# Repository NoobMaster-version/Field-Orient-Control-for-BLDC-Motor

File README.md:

# Field-Orient-Control-for-BLDC-Motor

STM32G431 + DRV8311H BLDC control project using STM32CubeIDE.

## Main components
- `STM32G431CBT6` (MCU)
- `DRV8311H` (3-phase gate driver)
- `AS5600` (magnetic encoder)
- `LDL1117` (voltage regulator)

This repo includes:
- `firmware/3xPWM_FOC` (FOC firmware project)
- `firmware/Open_Loop_Test_DRV8311` (open-loop bring-up test)

## Hardware

### Soldered PCB

### Motor running (open-loop)

## PWM mode (3x PWM)

The firmware uses **3x PWM** with `TIM1` and complementary outputs to drive DRV8311:
- `INHA` from `PA8  (TIM1_CH1)`
- `INHB` from `PA9  (TIM1_CH2)`
- `INHC` from `PA10 (TIM1_CH3)`

- `INLA` from `PB13 (TIM1_CH1N)`
- `INLB` from `PB14 (TIM1_CH2N)`
- `INLC` from `PB15 (TIM1_CH3N)`

## Pin connections (STM32 -> DRV8311 / interface)

### Gate driver control
- `PA8  (TIM1_CH1)`  -> `INHA`
- `PA9  (TIM1_CH2)`  -> `INHB`
- `PA10 (TIM1_CH3)`  -> `INHC`

- `PB13 (TIM1_CH1N)` -> `INLA`
- `PB14 (TIM1_CH2N)` -> `INLB`
- `PB15 (TIM1_CH3N)` -> `INLC`

- `PC13 (GPIO)`      -> `nSLEEP`
- `PC14 (GPIO input)`-> `nFAULT` (pull-up)

### Current sensing
- `PA0 (ADC1_IN1)` -> `SOA`
- `PA1 (ADC2_IN2)` -> `SOB`
- `PA2 (ADC1_IN3)` -> `SOC`

### Encoder and debug
- `PA15 (I2C1_SCL)` -> AS5600 `SCL`
- `PB7  (I2C1_SDA)` -> AS5600 `SDA`
- `PB10 (USART3_TX)` -> UART TX (debug)
- `PB11 (USART3_RX)` -> UART RX (debug)

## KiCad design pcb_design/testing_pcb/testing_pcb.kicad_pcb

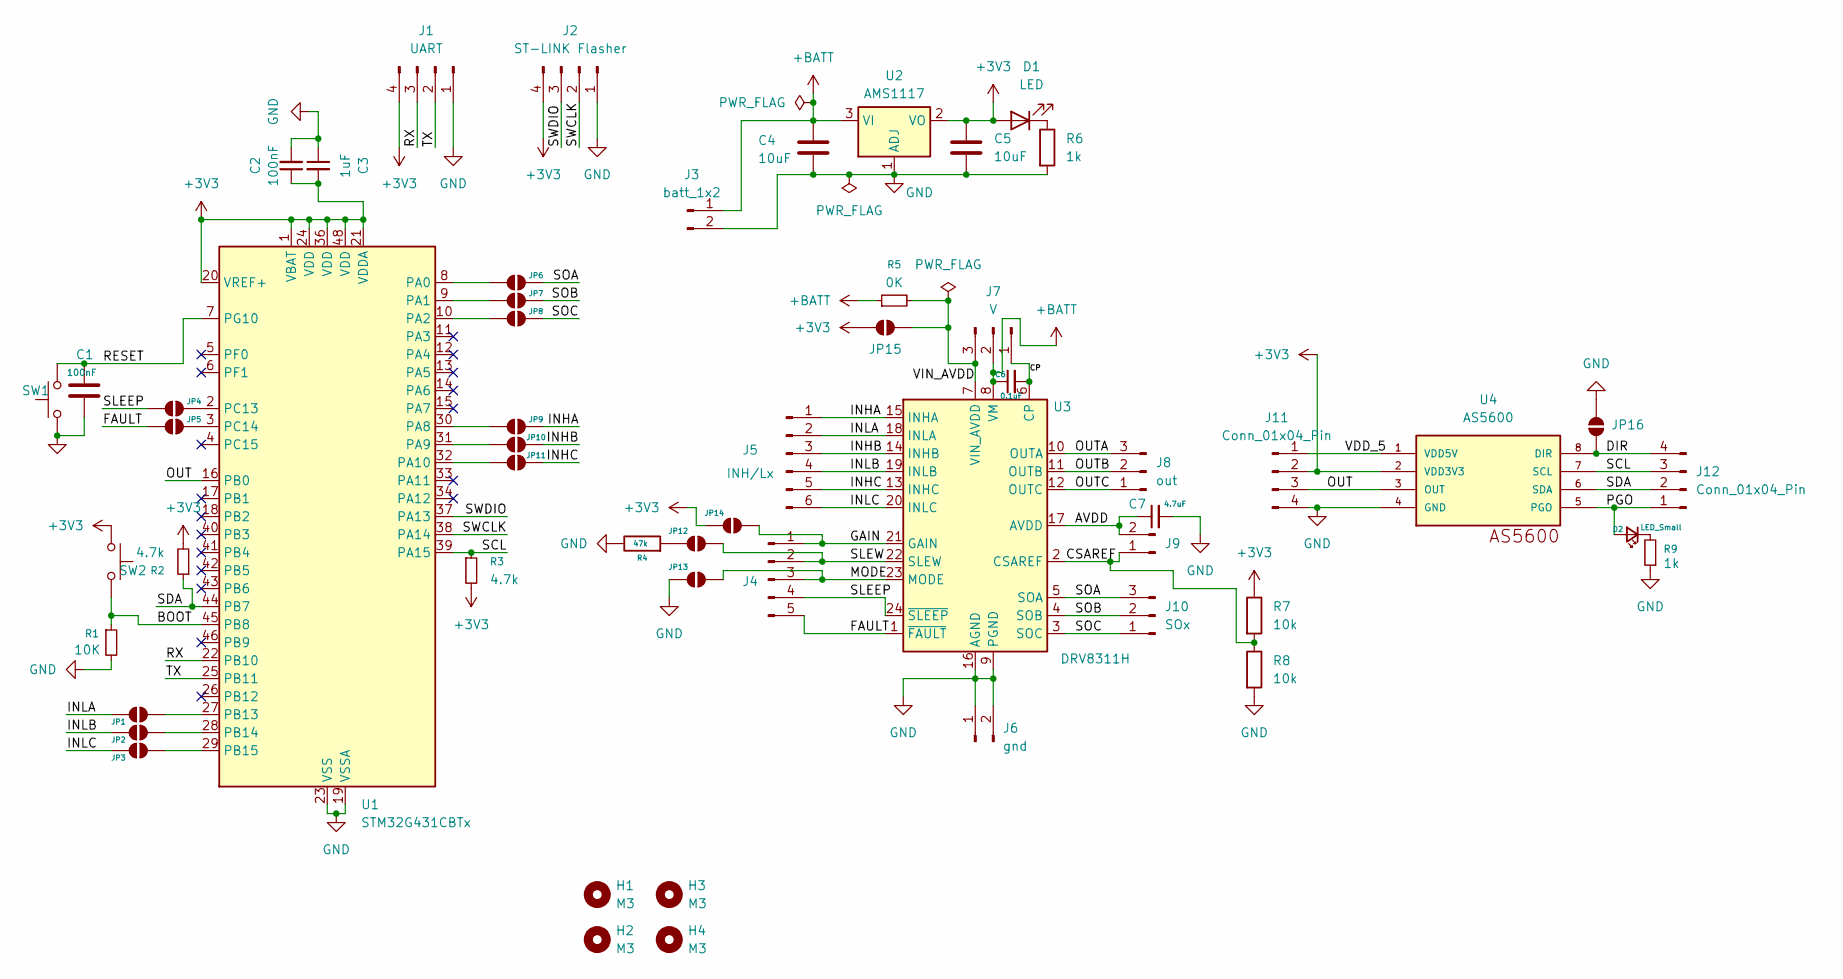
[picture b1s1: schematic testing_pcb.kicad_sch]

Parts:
C1: 100nF; C_0805_2012Metric_Pad1.18x1.45mm_HandSolder
C2: 100nF; C_0805_2012Metric
C3: 1uF; C_0805_2012Metric
C4, C5: 10uF; C_0805_2012Metric
C6: 0.1uF; C_0805_2012Metric
C7: 4.7uF; C_0805_2012Metric
D1: LED; LED_0805_2012Metric
D2: LED_Small; LED_0805_2012Metric
H1, H2, H3, H4: M3; MountingHole_3mm
J1: UART; PinSocket_1x04_P2.54mm_Vertical
J2: ST-LINK Flasher; PinSocket_1x04_P2.54mm_Vertical
J3: batt_1x2; PinSocket_1x02_P2.54mm_Vertical
J4: PinSocket_1x05_P2.54mm_Vertical
J5: INH/Lx; PinSocket_1x06_P2.54mm_Vertical
J6: gnd; PinSocket_1x02_P2.54mm_Vertical
J7: V; PinSocket_1x03_P2.54mm_Vertical
J8: out; PinSocket_1x03_P2.54mm_Vertical
J9: PinSocket_1x02_P2.54mm_Vertical
J10: SOx; PinSocket_1x03_P2.54mm_Vertical
J11, J12: Conn_01x04_Pin; PinSocket_1x04_P2.54mm_Vertical
JP1, JP2, JP3, JP4, JP5, JP6, JP7, JP8, JP9, JP10, JP11, JP12, JP13, JP14, JP15, JP16: SolderJumper_2_Open; SolderJumper-2_P1.3mm_Open_RoundedPad1.0x1.5mm
R1: 10K; R_0805_2012Metric
R2, R3: 4.7k; R_0805_2012Metric
R4: 47k; R_0805_2012Metric
R5: 0K; R_0805_2012Metric
R6: 1k; R_0805_2012Metric
R7, R8: 10k; R_0805_2012Metric
R9: 1k; LED_0805_2012Metric
SW1, SW2: SW_Push; SW_PUSH_6mm_H5mm
U1: STM32G431CBTx; LQFP-48_7x7mm_P0.5mm
U2: AMS1117; SOT-223-3_TabPin2
U3: DRV8311H; Texas_RRW0024A_WQFN-24-1EP_3x3mm_P0.4mm_EP1.9x1.9mm
U4: AS5600; SOIC8

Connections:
+3V3: C2.1, C3.2, C5.1, D1.2 (A), J1.4, J2.4, J11.2, JP14.1 (A), JP15.1 (A), R2.2, R3.2, R7.1, SW2.1, U1.1 (VBAT), U1.20 (VREF+), U1.21 (VDDA), U1.24 (VDD), U1.36 (VDD), U1.48 (VDD), U2.2 (VO), U4.2 (VDD3V3); also elsewhere on the board
+BATT: C4.1, C6.1, J3.1, J7.2, R5.1, U2.3 (VI), U3.8 (VM)
/AVDD: C7.1, J9.2, U3.17 (AVDD)
/BOOT: R1.1, SW2.2, U1.45 (PB8); also elsewhere on the board
/CP: C6.2, J7.1, U3.6 (CP)
/CSAREF: J9.1, R7.2, R8.1, U3.2 (CSAREF)
/DIR: J12.4, JP16.1 (A), U4.8 (DIR)
/FAULT: J4.5, JP5.1 (A), U3.1 (~FAULT)
/GAIN: J4.1, JP14.2 (B), U3.21 (GAIN)
/INHA: J5.1, JP9.2 (B), U3.15 (INHA)
/INHB: J5.3, JP10.2 (B), U3.14 (INHB)
/INHC: J5.5, JP11.2 (B), U3.13 (INHC)
/INLA: J5.2, JP1.2 (B), U3.18 (INLA)
/INLB: J5.4, JP2.2 (B), U3.19 (INLB)
/INLC: J5.6, JP3.2 (B), U3.20 (INLC)
/MODE: J4.3, JP13.2 (B), U3.23 (MODE)
/OUT: J11.3, U1.16 (PB0), U4.3 (OUT)
/OUTA: J8.3, U3.10 (OUTA)
/OUTB: J8.2, U3.11 (OUTB)
/OUTC: J8.1, U3.12 (OUTC)
/PGO: D2.2 (A), J12.1, U4.5 (PGO)
/RESET: C1.1, SW1.2, U1.7 (PG10); also elsewhere on the board
/RX: J1.3, U1.22 (PB10); also elsewhere on the board
/SCL: J12.3, R3.1, U1.39 (PA15), U4.7 (SCL)
/SDA: J12.2, R2.1, U1.44 (PB7), U4.6 (SDA)
/SLEEP: J4.4, JP4.1 (A), U3.24 (~SLEEP)
/SLEW: J4.2, JP12.2 (B), U3.22 (SLEW)
/SOA: J10.3, JP6.2 (B), U3.5 (SOA)
/SOB: J10.2, JP7.2 (B), U3.4 (SOB)
/SOC: J10.1, JP8.2 (B), U3.3 (SOC)
/SWCLK: J2.2, U1.38 (PA14)
/SWDIO: J2.3, U1.37 (PA13)
/TX: J1.2, U1.25 (PB11); also elsewhere on the board
/VDD_5: J11.1, U4.1 (VDD5V)
/VIN_AVDD: J7.3, JP15.2 (B), R5.2, U3.7 (VIN_AVDD)
GND: C1.2, C2.2, C3.1, C4.2, C5.2, C7.2, J1.1, J2.1, J3.2, J6.1, J6.2, J11.4, JP13.1 (A), JP16.2 (B), R1.2, R4.1, R6.2, R8.2, R9.1, SW1.1, U1.19 (VSSA), U1.23 (VSS), U1.35 (VSS), U1.47 (VSS), U2.1 (ADJ), U3.9 (PGND), U3.16 (AGND), U3.25 (PGND), U4.4 (GND); also elsewhere on the board
unnamed: D1.1 (K), R6.1
unnamed: D2.1 (K), R9.2
unnamed: JP1.1 (A), U1.27 (PB13)
unnamed: JP2.1 (A), U1.28 (PB14)
unnamed: JP3.1 (A), U1.29 (PB15)
unnamed: JP4.2 (B), U1.2 (PC13)
unnamed: JP5.2 (B), U1.3 (PC14)
unnamed: JP6.1 (A), U1.8 (PA0)
unnamed: JP7.1 (A), U1.9 (PA1)
unnamed: JP8.1 (A), U1.10 (PA2)
unnamed: JP9.1 (A), U1.30 (PA8)
unnamed: JP10.1 (A), U1.31 (PA9)
unnamed: JP11.1 (A), U1.32 (PA10)
unnamed: JP12.1 (A), R4.2

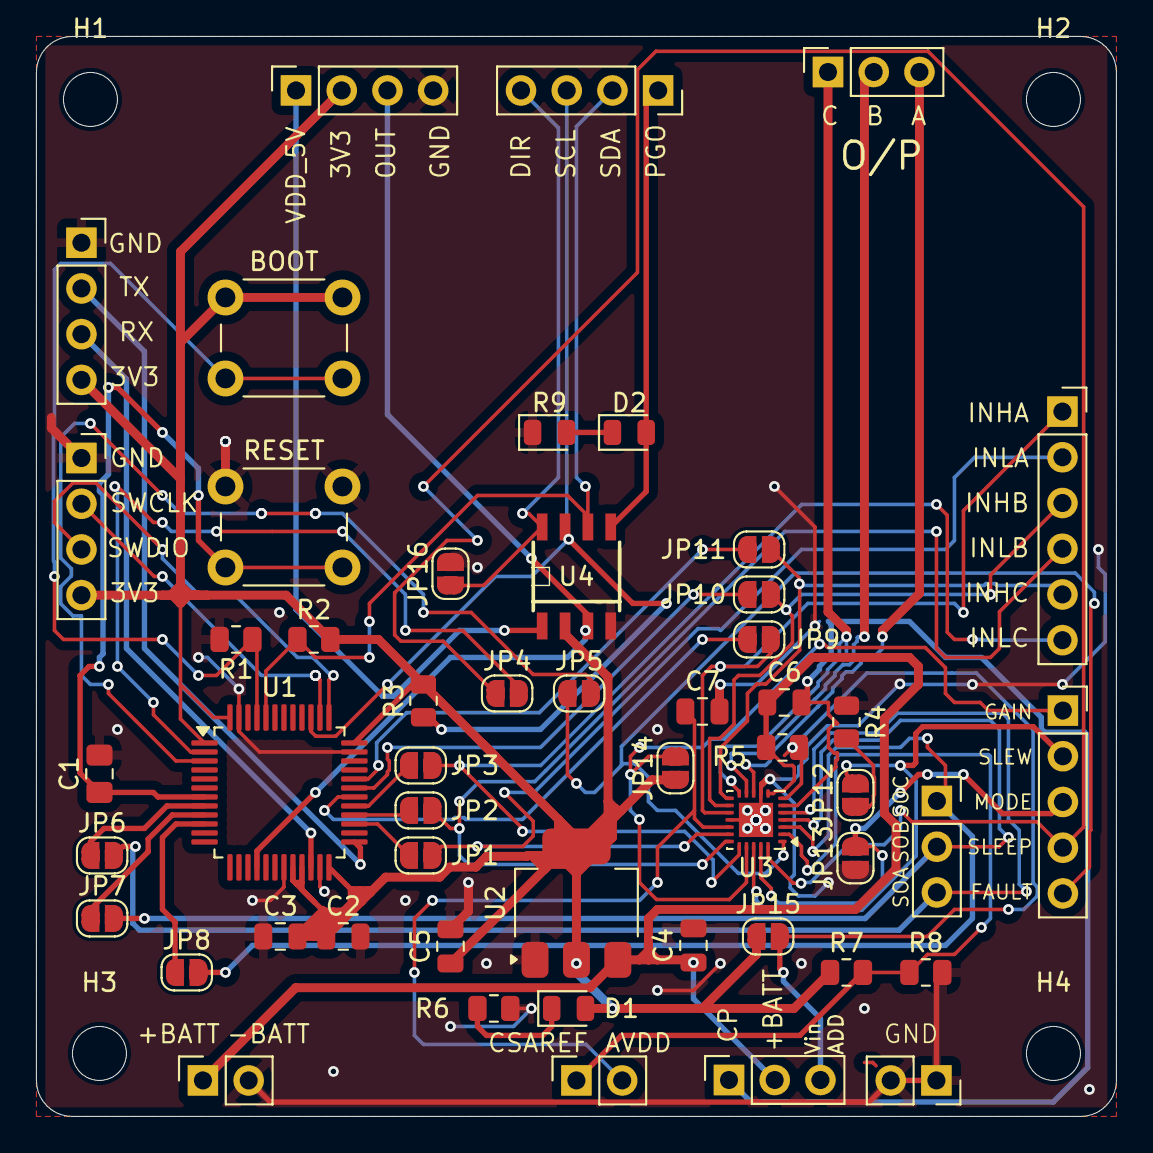
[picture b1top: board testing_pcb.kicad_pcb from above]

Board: 2 copper layers, 60.0 x 60.0 mm, 56 parts (0 on the bottom side), 50 nets.

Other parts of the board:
BOOT: SW_Push; SW_PUSH_6mm_H5mm
GND: UART; PinSocket_1x04_P2.54mm_Vertical
RESET: SW_Push; SW_PUSH_6mm_H5mm

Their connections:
+3V3: BOOT.1, GND.4; also elsewhere on the board
/BOOT: BOOT.2; also elsewhere on the board
/RESET: RESET.2; also elsewhere on the board
/RX: GND.3; also elsewhere on the board
/TX: GND.2; also elsewhere on the board
GND: GND.1, RESET.1; also elsewhere on the board

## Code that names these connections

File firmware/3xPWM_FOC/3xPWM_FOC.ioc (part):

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Mcu.Name=STM32G431C(6-8-B)Tx
Mcu.Package=LQFP48
Mcu.UserName=STM32G431CBTx
PA0.Mode=IN1-Single-Ended
PA0.Signal=ADC1_IN1
PA1.Mode=IN2-Single-Ended
PA1.Signal=ADC2_IN2
PA10.Signal=S_TIM1_CH3
PA15.Mode=I2C
PA15.Signal=I2C1_SCL
PA2.Mode=IN3-Single-Ended
PA2.Signal=ADC1_IN3
PA8.Signal=S_TIM1_CH1
PA9.Signal=S_TIM1_CH2
PB10.Mode=Asynchronous
PB10.Signal=USART3_TX
PB11.Mode=Asynchronous
PB11.Signal=USART3_RX
PB13.GPIOParameters=PinState,GPIO_Speed
PB13.PinState=GPIO_PIN_RESET
PB13.GPIO_Speed=GPIO_SPEED_FREQ_HIGH
PB13.Signal=GPIO_Output
PB14.GPIOParameters=PinState
PB14.PinState=GPIO_PIN_RESET
PB14.Signal=GPIO_Output
PB15.GPIOParameters=PinState
PB15.PinState=GPIO_PIN_RESET
PB15.Signal=GPIO_Output
PB7.Mode=I2C
PB7.Signal=I2C1_SDA
PC13.GPIOParameters=PinState
PC13.PinState=GPIO_PIN_RESET
PC13.Signal=GPIO_Output
PC14-OSC32_IN.GPIOParameters=GPIO_PuPd
PC14-OSC32_IN.GPIO_PuPd=GPIO_PULLUP
PC14-OSC32_IN.Signal=GPIO_Input
RCC.HSE_VALUE=8000000
RCC.SYSCLKFreq_VALUE=170000000
RCC.SYSCLKSource=RCC_SYSCLKSOURCE_PLLCLK
board=custom

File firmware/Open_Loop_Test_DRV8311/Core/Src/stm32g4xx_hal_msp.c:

/* USER CODE BEGIN Header */
/**
  ******************************************************************************
  * @file    stm32g4xx_hal_msp.c
  * @brief   MSP for DRV8311H 3x PWM + AS5600 encoder
  *
  * ============================================================
  *  FIX vs original hal_msp.c
  * ============================================================
  * BUG (original): HAL_TIM_MspPostInit initialised PB13/14/15 LOW with
  *   the comment "3x PWM MODE: INLx MUST be LOW". This is WRONG for the
  *   independent 3x PWM mode used here.
  *
  *   In DRV8311H 3x PWM mode the MCU drives INHx AND INLx independently:
  *     INLx=0 + INHx=0  → Hi-Z   (floating phase)
  *     INLx=1 + INHx=1  → H      (high-side ON)
  *     INLx=1 + INHx=0  → L      (low-side ON)
  *   apply_commutation_step() in main.c sets INLx correctly per step.
  *
  *   If MspPostInit forces INLx LOW after main.c has already set up the
  *   GPIO pins, every commutation step that relies on INLx=HIGH becomes
  *   broken: no current flows through the low-side phase, the motor gets
  *   no torque in those steps, and it vibrates/rocks instead of spinning.
  *
  *   FIX: HAL_TIM_MspPostInit now ONLY configures the AF PWM pins
  *   (PA8/PA9/PA10). The INLx GPIO direction is still set here so the
  *   pin is correctly initialised as an output, but the initial level is
  *   LOW (Hi-Z), and main.c / apply_commutation_step() takes full
  *   ownership of their runtime state.
  *
  * Peripherals initialised here:
  *   ADC1   PB0        ADC1_IN15  analog   AS5600 analog OUT
  *   I2C1   PA15/PB7   AF4        100kHz   AS5600 I2C
  *   TIM1   PA8/9/10   AF6        PWM      INHA/INHB/INHC
  *          PB13/14/15 GPIO LOW            INLA/INLB/INLC (runtime by main.c)
  *   USART3 PB10/11    AF7        115200   debug UART
  ******************************************************************************
  */
/* USER CODE END Header */

#include "main.h"

void HAL_TIM_MspPostInit(TIM_HandleTypeDef *htim);

void HAL_MspInit(void)
{
    __HAL_RCC_SYSCFG_CLK_ENABLE();
    __HAL_RCC_PWR_CLK_ENABLE();
    HAL_PWREx_DisableUCPDDeadBattery();
}

/* ===========================================================================
 * ADC1 — PB0 = ADC1_IN15 — AS5600 analog OUT
 * No DMA needed — continuous free-running, polled with HAL_ADC_GetValue()
 * =========================================================================*/
void HAL_ADC_MspInit(ADC_HandleTypeDef* hadc)
{
    GPIO_InitTypeDef         GPIO_InitStruct = {0};
    RCC_PeriphCLKInitTypeDef PeriphClkInit   = {0};

    if (hadc->Instance == ADC1)
    {
        PeriphClkInit.PeriphClockSelection = RCC_PERIPHCLK_ADC12;
        PeriphClkInit.Adc12ClockSelection  = RCC_ADC12CLKSOURCE_SYSCLK;
        if (HAL_RCCEx_PeriphCLKConfig(&PeriphClkInit) != HAL_OK) Error_Handler();

        __HAL_RCC_ADC12_CLK_ENABLE();
        __HAL_RCC_GPIOB_CLK_ENABLE();

        GPIO_InitStruct.Pin  = GPIO_PIN_0;
        GPIO_InitStruct.Mode = GPIO_MODE_ANALOG;
        GPIO_InitStruct.Pull = GPIO_NOPULL;
        HAL_GPIO_Init(GPIOB, &GPIO_InitStruct);
    }
}

void HAL_ADC_MspDeInit(ADC_HandleTypeDef* hadc)
{
    if (hadc->Instance == ADC1)
    {
        __HAL_RCC_ADC12_CLK_DISABLE();
        HAL_GPIO_DeInit(GPIOB, GPIO_PIN_0);
    }
}

/* ===========================================================================
 * I2C1 — PA15=SCL(AF4)  PB7=SDA(AF4)
 * =========================================================================*/
void HAL_I2C_MspInit(I2C_HandleTypeDef* hi2c)
{
    GPIO_InitTypeDef         GPIO_InitStruct = {0};
    RCC_PeriphCLKInitTypeDef PeriphClkInit   = {0};

    if (hi2c->Instance == I2C1)
    {
        PeriphClkInit.PeriphClockSelection = RCC_PERIPHCLK_I2C1;
        PeriphClkInit.I2c1ClockSelection   = RCC_I2C1CLKSOURCE_PCLK1;
        if (HAL_RCCEx_PeriphCLKConfig(&PeriphClkInit) != HAL_OK) Error_Handler();

        __HAL_RCC_GPIOA_CLK_ENABLE();
        __HAL_RCC_GPIOB_CLK_ENABLE();

        /* PA15 → I2C1_SCL */
        GPIO_InitStruct.Pin       = GPIO_PIN_15;
        GPIO_InitStruct.Mode      = GPIO_MODE_AF_OD;
        GPIO_InitStruct.Pull      = GPIO_NOPULL;
        GPIO_InitStruct.Speed     = GPIO_SPEED_FREQ_LOW;
        GPIO_InitStruct.Alternate = GPIO_AF4_I2C1;
        HAL_GPIO_Init(GPIOA, &GPIO_InitStruct);

        /* PB7 → I2C1_SDA */
        GPIO_InitStruct.Pin       = GPIO_PIN_7;
        GPIO_InitStruct.Mode      = GPIO_MODE_AF_OD;
        GPIO_InitStruct.Pull      = GPIO_NOPULL;
        GPIO_InitStruct.Speed     = GPIO_SPEED_FREQ_LOW;
        GPIO_InitStruct.Alternate = GPIO_AF4_I2C1;
        HAL_GPIO_Init(GPIOB, &GPIO_InitStruct);

        __HAL_RCC_I2C1_CLK_ENABLE();
    }
}

void HAL_I2C_MspDeInit(I2C_HandleTypeDef* hi2c)
{
    if (hi2c->Instance == I2C1)
    {
        __HAL_RCC_I2C1_CLK_DISABLE();
        HAL_GPIO_DeInit(GPIOA, GPIO_PIN_15);
        HAL_GPIO_DeInit(GPIOB, GPIO_PIN_7);
    }
}

/* ===========================================================================
 * TIM1 base clock
 * =========================================================================*/
void HAL_TIM_Base_MspInit(TIM_HandleTypeDef* htim_base)
{
    if (htim_base->Instance == TIM1)
        __HAL_RCC_TIM1_CLK_ENABLE();
}

void HAL_TIM_Base_MspDeInit(TIM_HandleTypeDef* htim_base)
{
    if (htim_base->Instance == TIM1)
        __HAL_RCC_TIM1_CLK_DISABLE();
}

/* ===========================================================================
 * HAL_TIM_MspPostInit — GPIO for TIM1 PWM outputs + INLx direction only
 *
 * PA8/PA9/PA10 → TIM1 CH1/2/3 (INHA/INHB/INHC) AF6  [PWM outputs]
 * PB13/14/15   → INLA/INLB/INLC GPIO output, initialised LOW (Hi-Z)
 *
 * !! DO NOT force INLx HIGH here !!
 * In DRV8311H independent 3x PWM mode:
 *   INLx = 0  → that phase's low-side FET is OFF  → combined with INHx=0 = Hi-Z
 *   INLx = 1  → low-side FET is enabled by INHx state
 * apply_commutation_step() in main.c sets INLx per commutation step at
 * runtime. This function only sets the GPIO direction; it must not override
 * the runtime INLx level.
 * =========================================================================*/
void HAL_TIM_MspPostInit(TIM_HandleTypeDef* htim)
{
    GPIO_InitTypeDef GPIO_InitStruct = {0};

    if (htim->Instance == TIM1)
    {
        __HAL_RCC_GPIOA_CLK_ENABLE();

        /* PA8/PA9/PA10 → TIM1 CH1/2/3 AF6 (INHA/INHB/INHC) */
        GPIO_InitStruct.Pin       = GPIO_PIN_8 | GPIO_PIN_9 | GPIO_PIN_10;
        GPIO_InitStruct.Mode      = GPIO_MODE_AF_PP;
        GPIO_InitStruct.Pull      = GPIO_NOPULL;
        GPIO_InitStruct.Speed     = GPIO_SPEED_FREQ_HIGH;
        GPIO_InitStruct.Alternate = GPIO_AF6_TIM1;
        HAL_GPIO_Init(GPIOA, &GPIO_InitStruct);

        /* PB13/14/15 → INLA/INLB/INLC
         * Direction: output push-pull.
         * Initial level: LOW (all phases Hi-Z at power-on).
         * Runtime level: controlled exclusively by apply_commutation_step()
         *                in main.c — do NOT set HIGH here.                  */
        __HAL_RCC_GPIOB_CLK_ENABLE();
        HAL_GPIO_WritePin(GPIOB,
                          GPIO_PIN_13 | GPIO_PIN_14 | GPIO_PIN_15,
                          GPIO_PIN_RESET);   /* LOW = Hi-Z at startup */
        GPIO_InitStruct.Pin       = GPIO_PIN_13 | GPIO_PIN_14 | GPIO_PIN_15;
        GPIO_InitStruct.Mode      = GPIO_MODE_OUTPUT_PP;
        GPIO_InitStruct.Pull      = GPIO_NOPULL;
        GPIO_InitStruct.Speed     = GPIO_SPEED_FREQ_LOW;
        GPIO_InitStruct.Alternate = 0;
        HAL_GPIO_Init(GPIOB, &GPIO_InitStruct);
    }
}

/* ===========================================================================
 * USART3 — PB10=TX(AF7)  PB11=RX(AF7)
 * =========================================================================*/
void HAL_UART_MspInit(UART_HandleTypeDef* huart)
{
    GPIO_InitTypeDef         GPIO_InitStruct = {0};
    RCC_PeriphCLKInitTypeDef PeriphClkInit   = {0};

    if (huart->Instance == USART3)
    {
        PeriphClkInit.PeriphClockSelection  = RCC_PERIPHCLK_USART3;
        PeriphClkInit.Usart3ClockSelection  = RCC_USART3CLKSOURCE_PCLK1;
        if (HAL_RCCEx_PeriphCLKConfig(&PeriphClkInit) != HAL_OK) Error_Handler();

        __HAL_RCC_USART3_CLK_ENABLE();
        __HAL_RCC_GPIOB_CLK_ENABLE();

        GPIO_InitStruct.Pin       = GPIO_PIN_10 | GPIO_PIN_11;
        GPIO_InitStruct.Mode      = GPIO_MODE_AF_PP;
        GPIO_InitStruct.Pull      = GPIO_NOPULL;
        GPIO_InitStruct.Speed     = GPIO_SPEED_FREQ_LOW;
        GPIO_InitStruct.Alternate = GPIO_AF7_USART3;
        HAL_GPIO_Init(GPIOB, &GPIO_InitStruct);
    }
}

void HAL_UART_MspDeInit(UART_HandleTypeDef* huart)
{
    if (huart->Instance == USART3)
    {
        __HAL_RCC_USART3_CLK_DISABLE();
        HAL_GPIO_DeInit(GPIOB, GPIO_PIN_10 | GPIO_PIN_11);
    }
}

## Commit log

2026-01-28 Added circuit for DRV8311 and AS5600
2026-02-04 test pcb updated
2026-02-05 added round corners , fixed acute angle turns
2026-03-19 Added 3xPWM firmware with AS5600 support Updated README.md
2026-03-20 6 commutation 4300kv
2026-04-08 added basic zephyr examples for the board
2026-04-08 overcurrent issue
